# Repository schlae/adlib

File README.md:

# adlib
Reproduction AdLib Sound Card, OPL2, Circa 1990

For details see http://tubetime.us/?p=419.

This is a (nearly) exact clone of the 1990 version of the AdLib sound card.

User root42 has created a Mouser project with the parts in the BOM at https://www.mouser.com/ProjectManager/ProjectDetail.aspx?AccessID=b0869fd937

This work is licensed under a Creative Commons Attribution 4.0 International License. See https://creativecommons.org/licenses/by/4.0/

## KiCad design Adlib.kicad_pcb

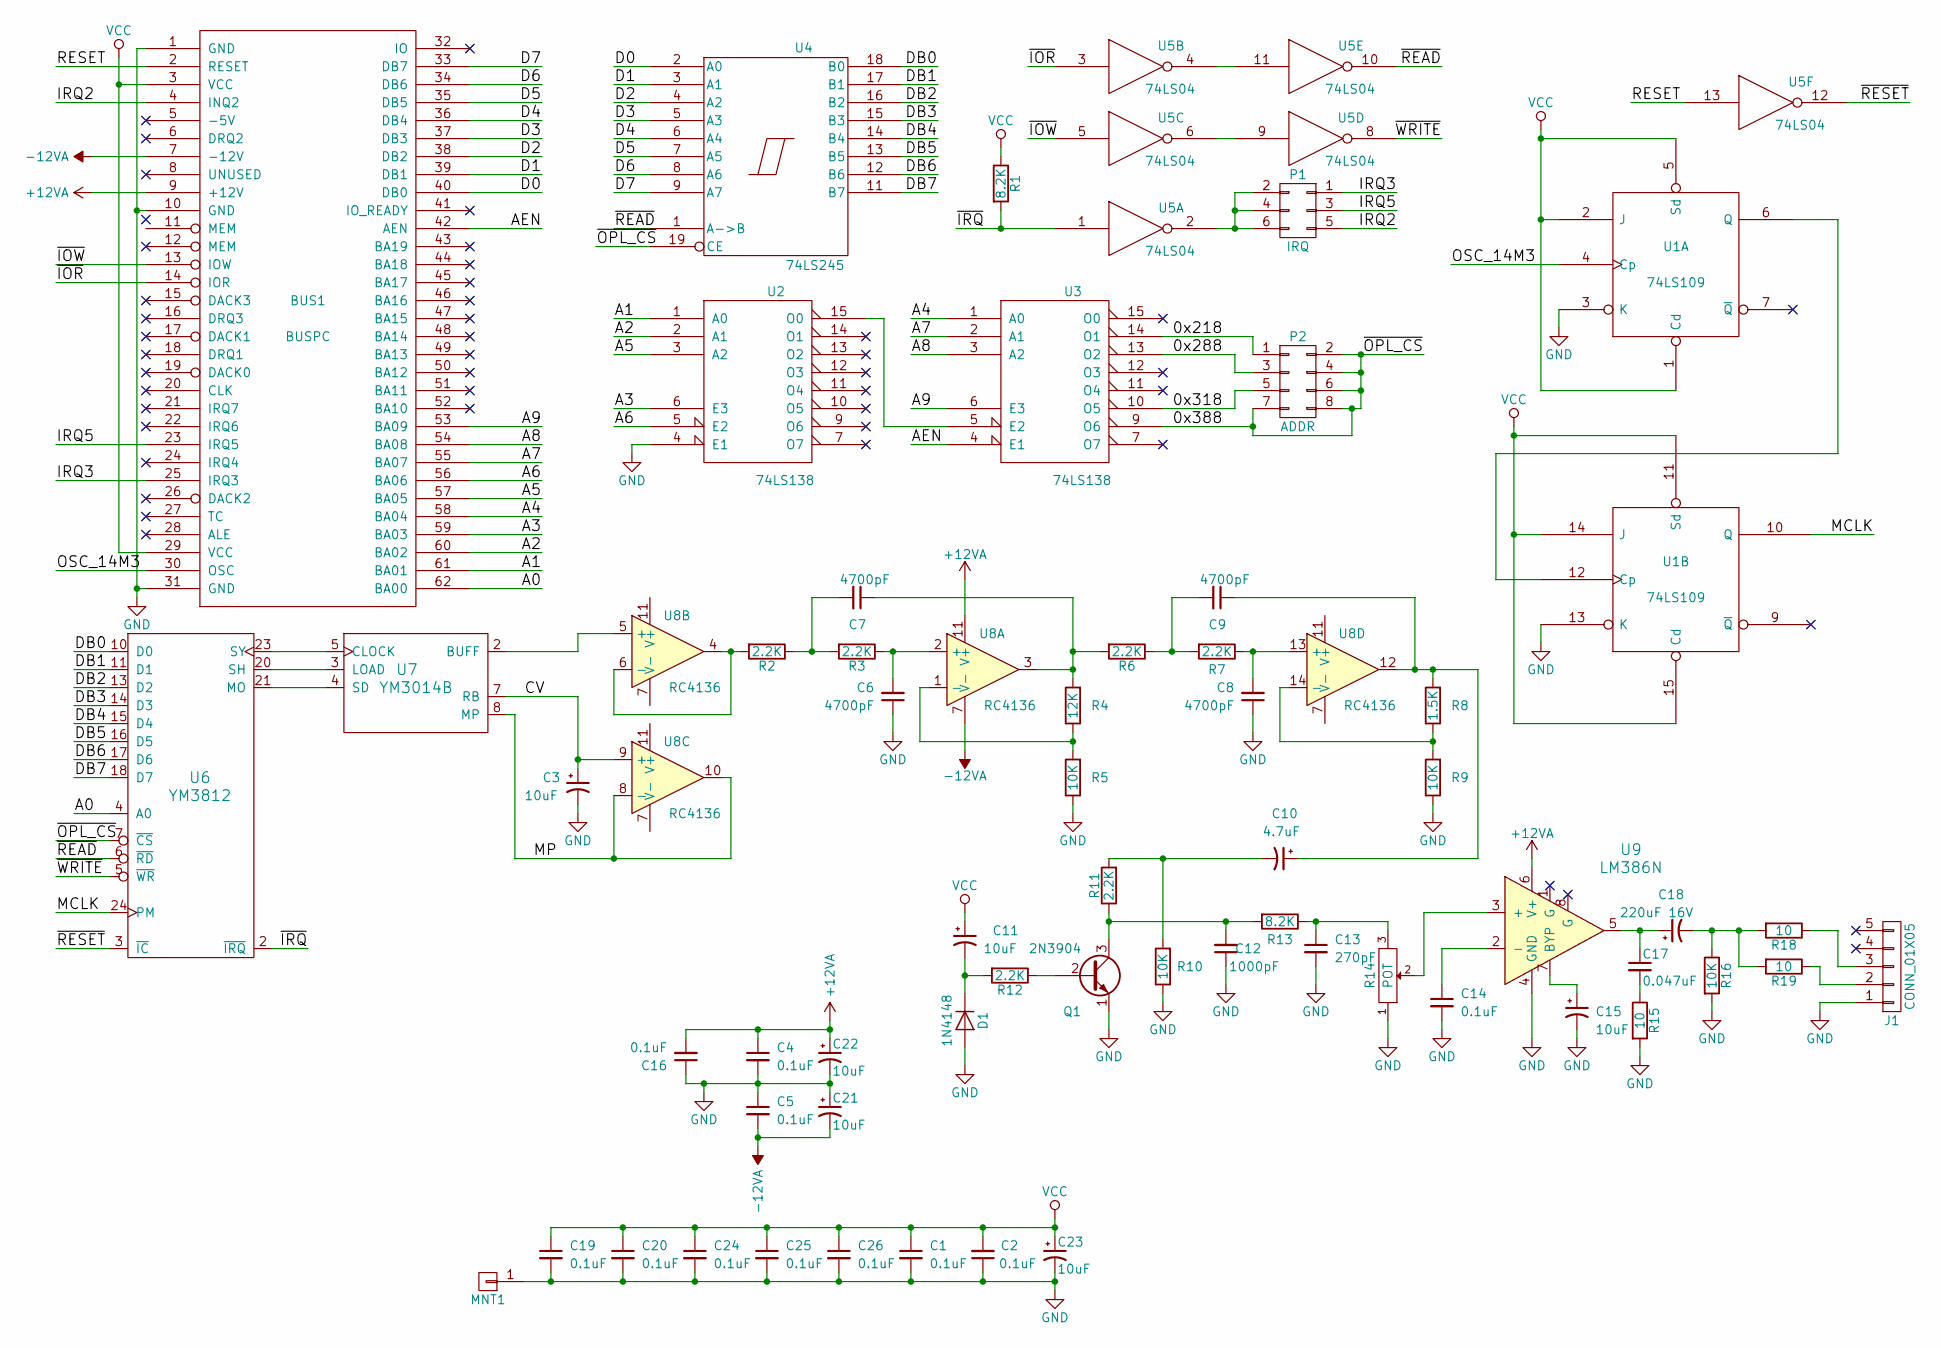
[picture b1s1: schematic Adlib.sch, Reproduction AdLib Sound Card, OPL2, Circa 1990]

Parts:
BUS1: BUSPC; BUS_PC_ADLIB
C1, C2, C4, C5, C14, C16, C19, C20, C24, C25, C26: 0.1uF; CAP23; Mouser 581-AR215C104K4R
C3, C11, C15, C21, C22, C23: 10uF; CAPAP200; Mouser 581-TAP106M025CRW
C6, C7, C8, C9: 4700pF; CAP23; Mouser 581-AR211C472K4R
C10: 4.7uF; CAPAP200; Mouser 581-TAP475K016SCS
C12: 1000pF; CAP23; Mouser 581-AR211C102K4R
C13: 270pF; CAP23; Mouser 594-S271K43SL0N6TK5R
C17: 0.047uF; CAP23; Mouser 581-AR215C473K4R
C18: 220uF 16V; CAPA1000; Mouser 647-TVX1C221MAD
D1: 1N4148; DIOA500; Mouser 512-1N4148
J1: CONN_01X05; JACK_CUI_SJ1-3553NG; Mouser 490-SJ1-3553NG
MNT1: CONN_01X01; MNT_KEYSTONE_9202; Mouser 534-9202
P1: IRQ; JMP3
P2: ADDR; JMP4
Q1: 2N3904; TO92-IL; Mouser 512-2N3904BU
R1, R13: 8.2K; RESA500; Mouser 291-8.2K-RC
R2, R3, R6, R7, R11, R12: 2.2K; RESA500; Mouser 291-2.2K-RC
R4: 12K; RESA500; Mouser 291-12K-RC
R5, R9, R10, R16: 10K; RESA500; Mouser 291-10K-RC
R8: 1.5K; RESA500; Mouser 291-1.5K-RC
R14: POT; RESV_BOURNS_91A1A; Mouser 652-91A1A-B24-D15L
R15, R18, R19: 10; RESA500; Mouser 291-10-RC
U1: 74LS109; DIP300_16N; Mouser 595-SN74LS109AN
U2, U3: 74LS138; DIP300_16N; Mouser 595-SN74LS138N
U4: 74LS245; DIP300_20N; Mouser 595-SN74LS245N
U5: 74LS04; DIP300_14N; Mouser 595-SN74LS04N
U6: YM3812; DIP600_24N
U7: YM3014B; DIP300_8N
U8: RC4136; DIP300_14N; Mouser 595-RC4136N
U9: LM386N; DIP300_8N; Mouser 926-LM386N-4/NOPB

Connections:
+12VA: BUS1.9 (+12V), C4.1, C16.2, C22.1, U8.11 (V+), U9.6 (V+)
-12VA: BUS1.7 (-12V), C5.2, C21.2, U8.7 (V-)
/0x218: P2.1, U3.14 (O1)
/0x288: P2.3, U3.13 (O2)
/0x318: P2.5, U3.10 (O5)
/0x388: P2.2, P2.4, P2.6, P2.7, P2.8, U3.9 (O6), U4.19 (CE), U6.7 (~CS)
/A0: BUS1.62 (BA00), U6.4 (A0)
/A1: BUS1.61 (BA01), U2.1 (A0)
/A2: BUS1.60 (BA02), U2.2 (A1)
/A3: BUS1.59 (BA03), U2.6 (E3)
/A4: BUS1.58 (BA04), U3.1 (A0)
/A5: BUS1.57 (BA05), U2.3 (A2)
/A6: BUS1.56 (BA06), U2.5 (E2)
/A7: BUS1.55 (BA07), U3.2 (A1)
/A8: BUS1.54 (BA08), U3.3 (A2)
/A9: BUS1.53 (BA09), U3.6 (E3)
/AEN: BUS1.42 (AEN), U3.4 (E1)
/CV: C3.1, U7.7 (RB), U8.9 (+)
/D0: BUS1.40 (DB0), U4.2 (A0)
/D1: BUS1.39 (DB1), U4.3 (A1)
/D2: BUS1.38 (DB2), U4.4 (A2)
/D3: BUS1.37 (DB3), U4.5 (A3)
/D4: BUS1.36 (DB4), U4.6 (A4)
/D5: BUS1.35 (DB5), U4.7 (A5)
/D6: BUS1.34 (DB6), U4.8 (A6)
/D7: BUS1.33 (DB7), U4.9 (A7)
/DB0: U4.18 (B0), U6.10 (D0)
/DB1: U4.17 (B1), U6.11 (D1)
/DB2: U4.16 (B2), U6.13 (D2)
/DB3: U4.15 (B3), U6.14 (D3)
/DB4: U4.14 (B4), U6.15 (D4)
/DB5: U4.13 (B5), U6.16 (D5)
/DB6: U4.12 (B6), U6.17 (D6)
/DB7: U4.11 (B7), U6.18 (D7)
/IRQ2: BUS1.4 (INQ2), P1.5
/IRQ3: BUS1.25 (IRQ3), P1.1
/IRQ5: BUS1.23 (IRQ5), P1.3
/MCLK: U1.10 (Q), U6.24 (PM)
/MP: U7.8 (MP), U8.8 (-), U8.10
/OSC_14M3: BUS1.30 (OSC), U1.4 (Cp)
/RESET: BUS1.2 (RESET), U5.13
/~IOR: BUS1.14 (IOR), U5.3
/~IOW: BUS1.13 (IOW), U5.5
/~IRQ: R1.2, U5.1, U6.2 (~IRQ)
/~READ: U4.1 (A->B), U5.10, U6.6 (~RD)
/~RESET: U5.12, U6.3 (~IC)
/~WRITE: U5.8, U6.5 (~WR)
GND: BUS1.1 (GND), BUS1.10 (GND), BUS1.31 (GND), C1.2, C2.1, C3.2, C4.2, C5.1, C6.1, C8.1, C12.1, C13.2, C14.2, C15.2, C16.1, C19.2, C20.2, C21.1, C22.2, C23.2, C24.2, C25.2, C26.2, D1.2 (A), J1.1, MNT1.1, Q1.1 (E), R5.1, R9.1, R10.1, R14.1, R15.2, R16.2, U1.3 (K), U1.8 (GND), U1.13 (K), U2.4 (E1), U2.8 (GND), U3.8 (GND), U4.10 (GND), U5.7 (GND), U6.12 (GND), U7.6 (GND), U9.4 (GND)
unnamed: C6.2, R3.1, U8.2 (+)
unnamed: C7.1, R4.2, R6.2, U8.3
unnamed: C7.2, R2.1, R3.2
unnamed: C8.2, R7.1, U8.13 (+)
unnamed: C9.2, R6.1, R7.2
unnamed: C9.1, C10.1, R8.2, U8.12
unnamed: C10.2, R10.2, R11.2
unnamed: C11.2, D1.1 (K), R12.2
unnamed: C12.2, Q1.3 (C), R11.1, R13.2
unnamed: C13.1, R13.1, R14.3
unnamed: C14.1, U9.2 (-)
unnamed: C15.1, U9.7 (BYP)
unnamed: C17.1, C18.1, U9.5
unnamed: C17.2, R15.1
unnamed: C18.2, R16.1, R18.2, R19.2
unnamed: J1.2, R19.1
unnamed: J1.3, R18.1
unnamed: P1.2, P1.4, P1.6, U5.2
unnamed: Q1.2 (B), R12.1
unnamed: R2.2, U8.4, U8.6 (-)
unnamed: R4.1, R5.2, U8.1 (-)
unnamed: R8.1, R9.2, U8.14 (-)
unnamed: R14.2, U9.3 (+)
unnamed: U1.6 (Q), U1.12 (Cp)
unnamed: U2.15 (O0), U3.5 (E2)
unnamed: U5.6, U5.9
unnamed: U5.4, U5.11
unnamed: U6.20 (SH), U7.3 (LOAD)
unnamed: U6.21 (MO), U7.4 (SD)
unnamed: U6.23 (SY), U7.5 (CLOCK)
unnamed: U7.2 (BUFF), U8.5 (+)
VCC: BUS1.3 (VCC), BUS1.29 (VCC), C1.1, C2.2, C11.1, C19.1, C20.1, C23.1, C24.1, C25.1, C26.1, R1.1, U1.1 (Cd), U1.2 (J), U1.5 (Sd), U1.11 (Sd), U1.14 (J), U1.15 (Cd), U1.16 (VCC), U2.16 (VCC), U3.16 (VCC), U4.20 (VCC), U5.14 (VCC), U6.1 (VCC), U7.1 (VCC)

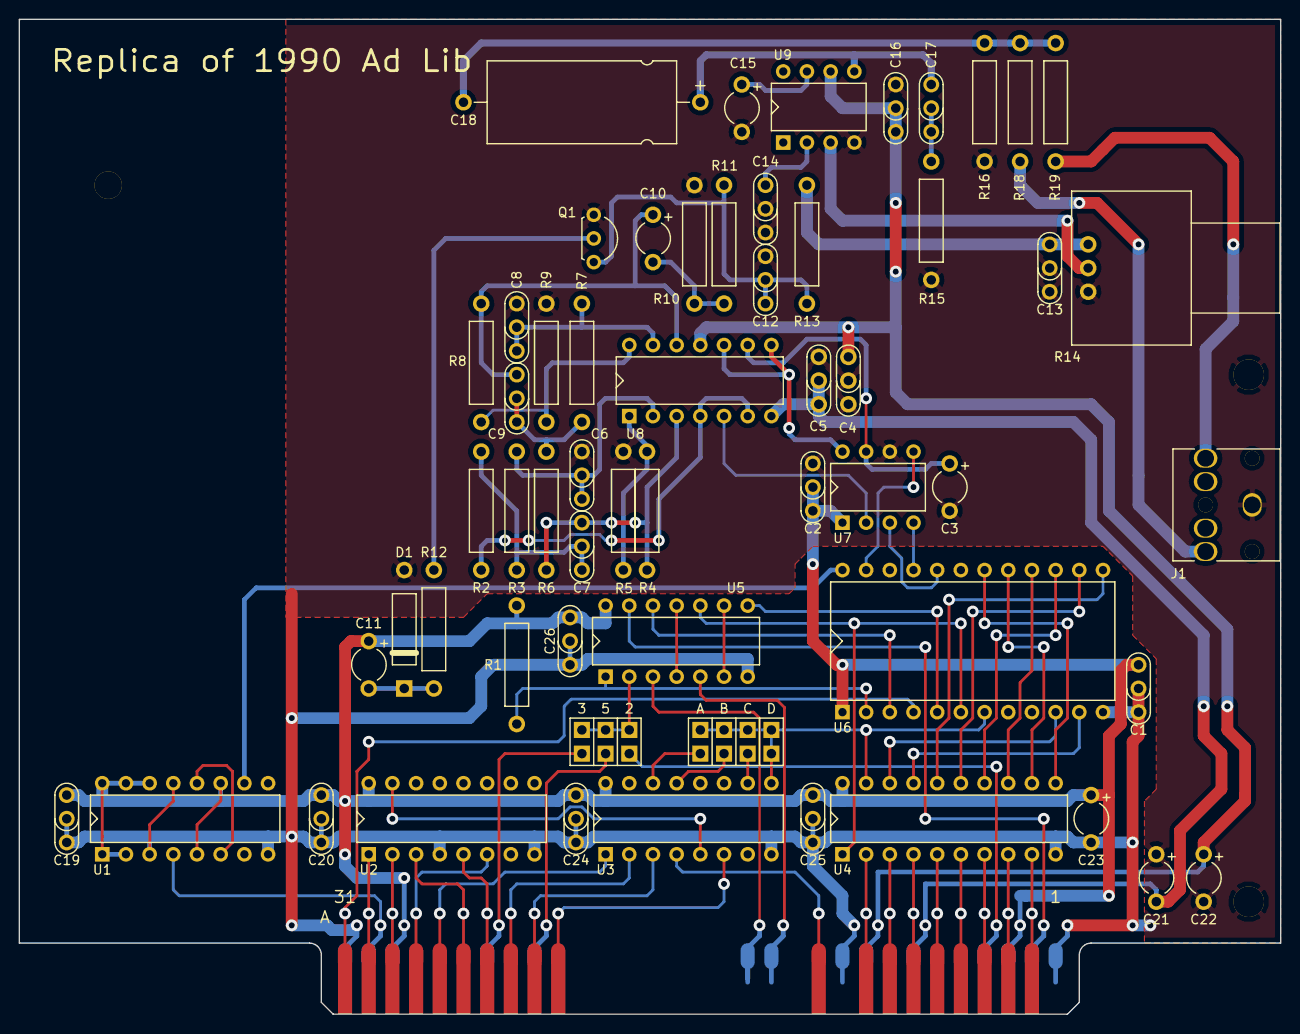
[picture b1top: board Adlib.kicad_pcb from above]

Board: 2 copper layers, 135.3 x 106.7 mm, 60 parts (0 on the bottom side), 80 nets.

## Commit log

2018-07-16 Updated layout.

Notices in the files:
Adlib.sch:
Copyright (C) 2017 Eric Schlaepfer
